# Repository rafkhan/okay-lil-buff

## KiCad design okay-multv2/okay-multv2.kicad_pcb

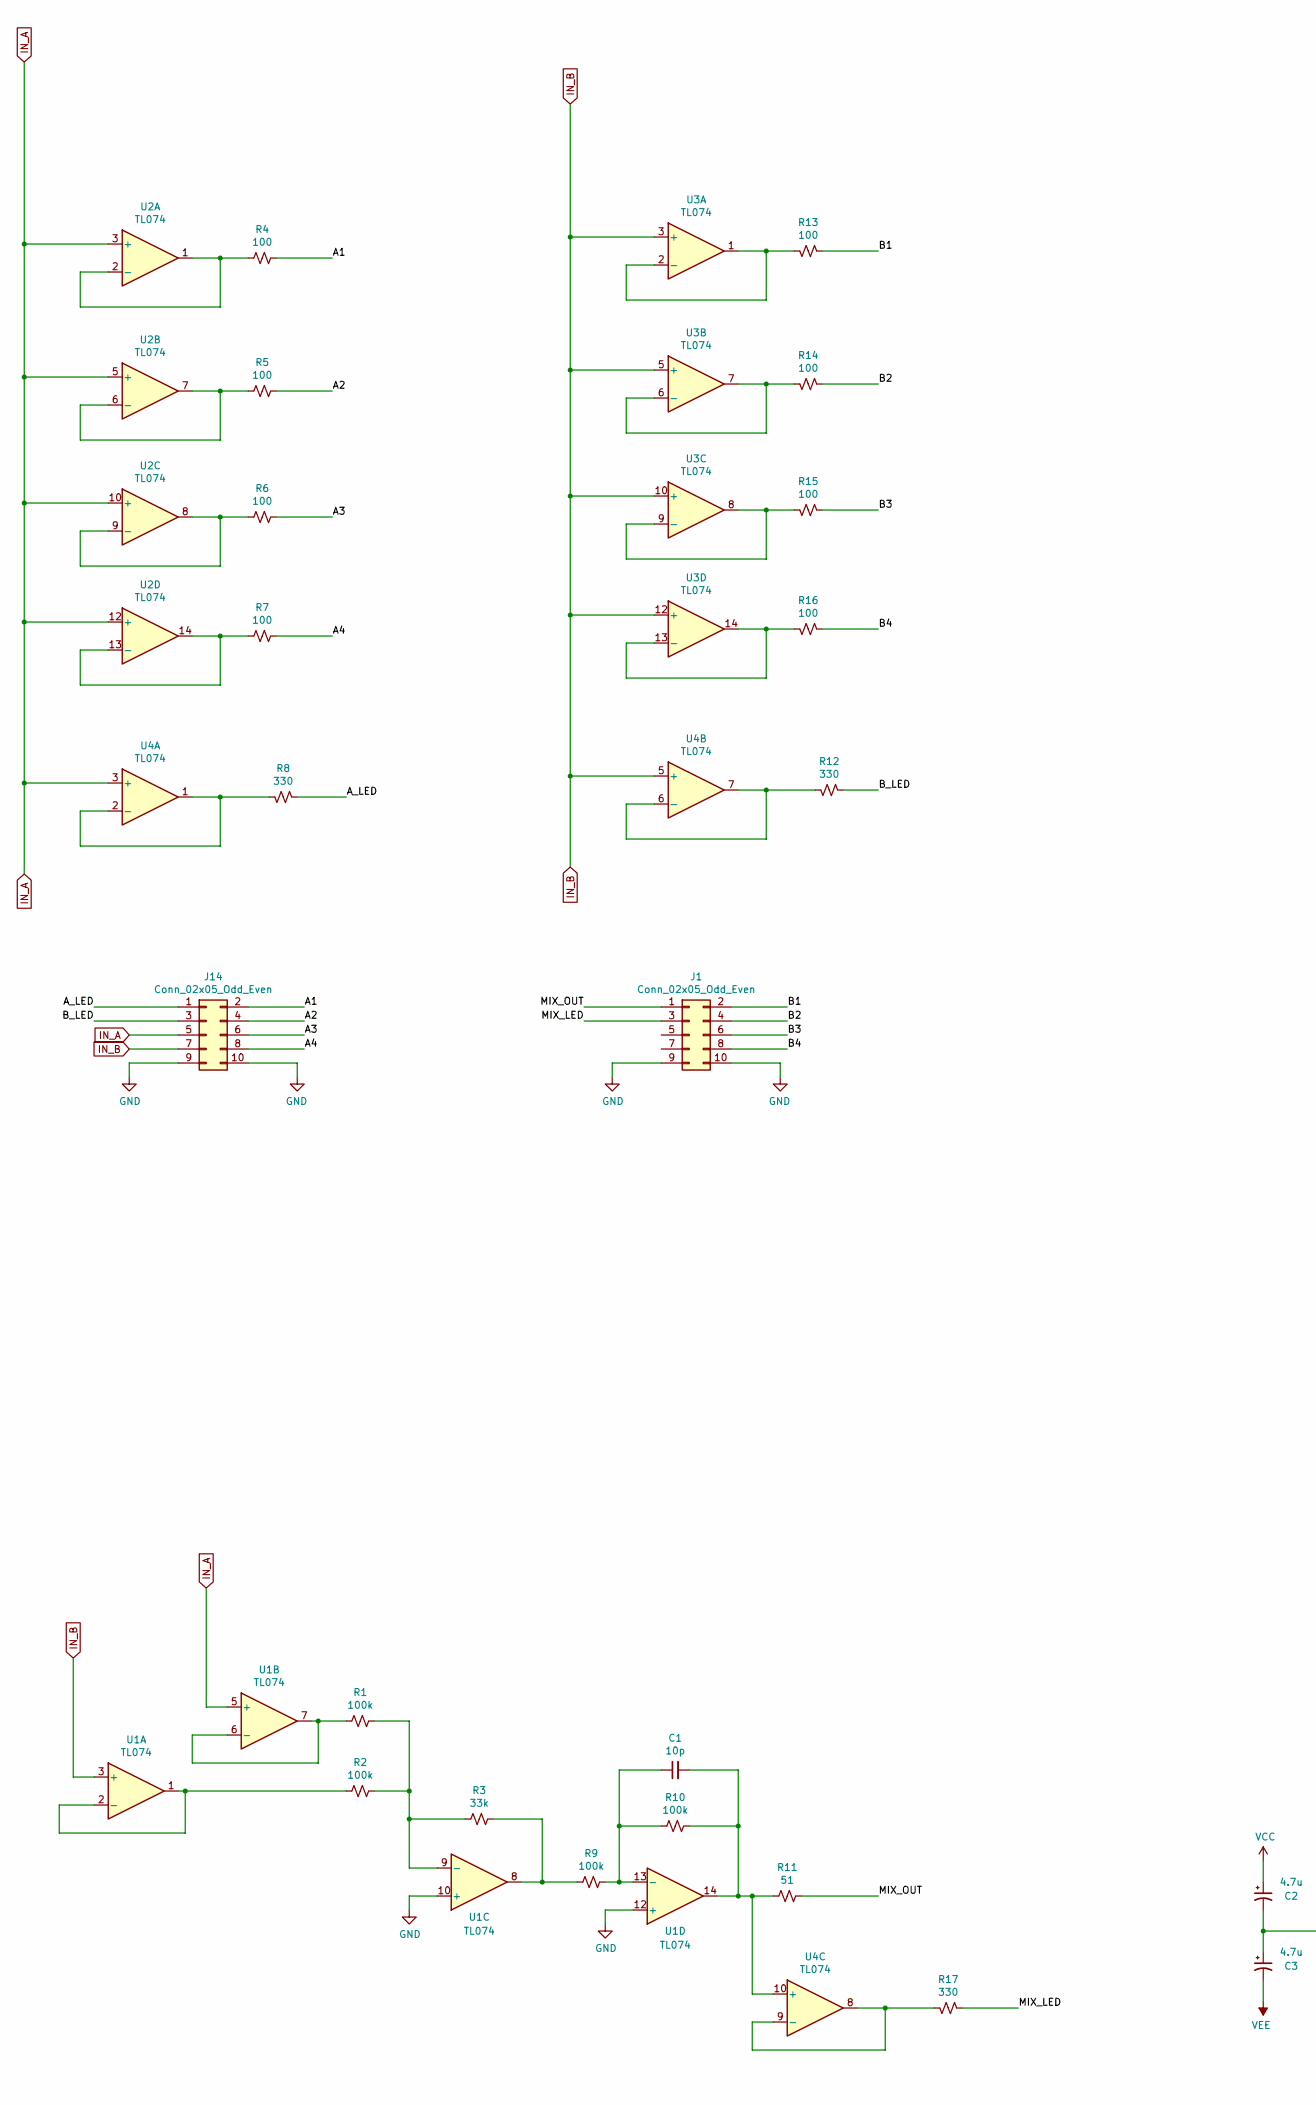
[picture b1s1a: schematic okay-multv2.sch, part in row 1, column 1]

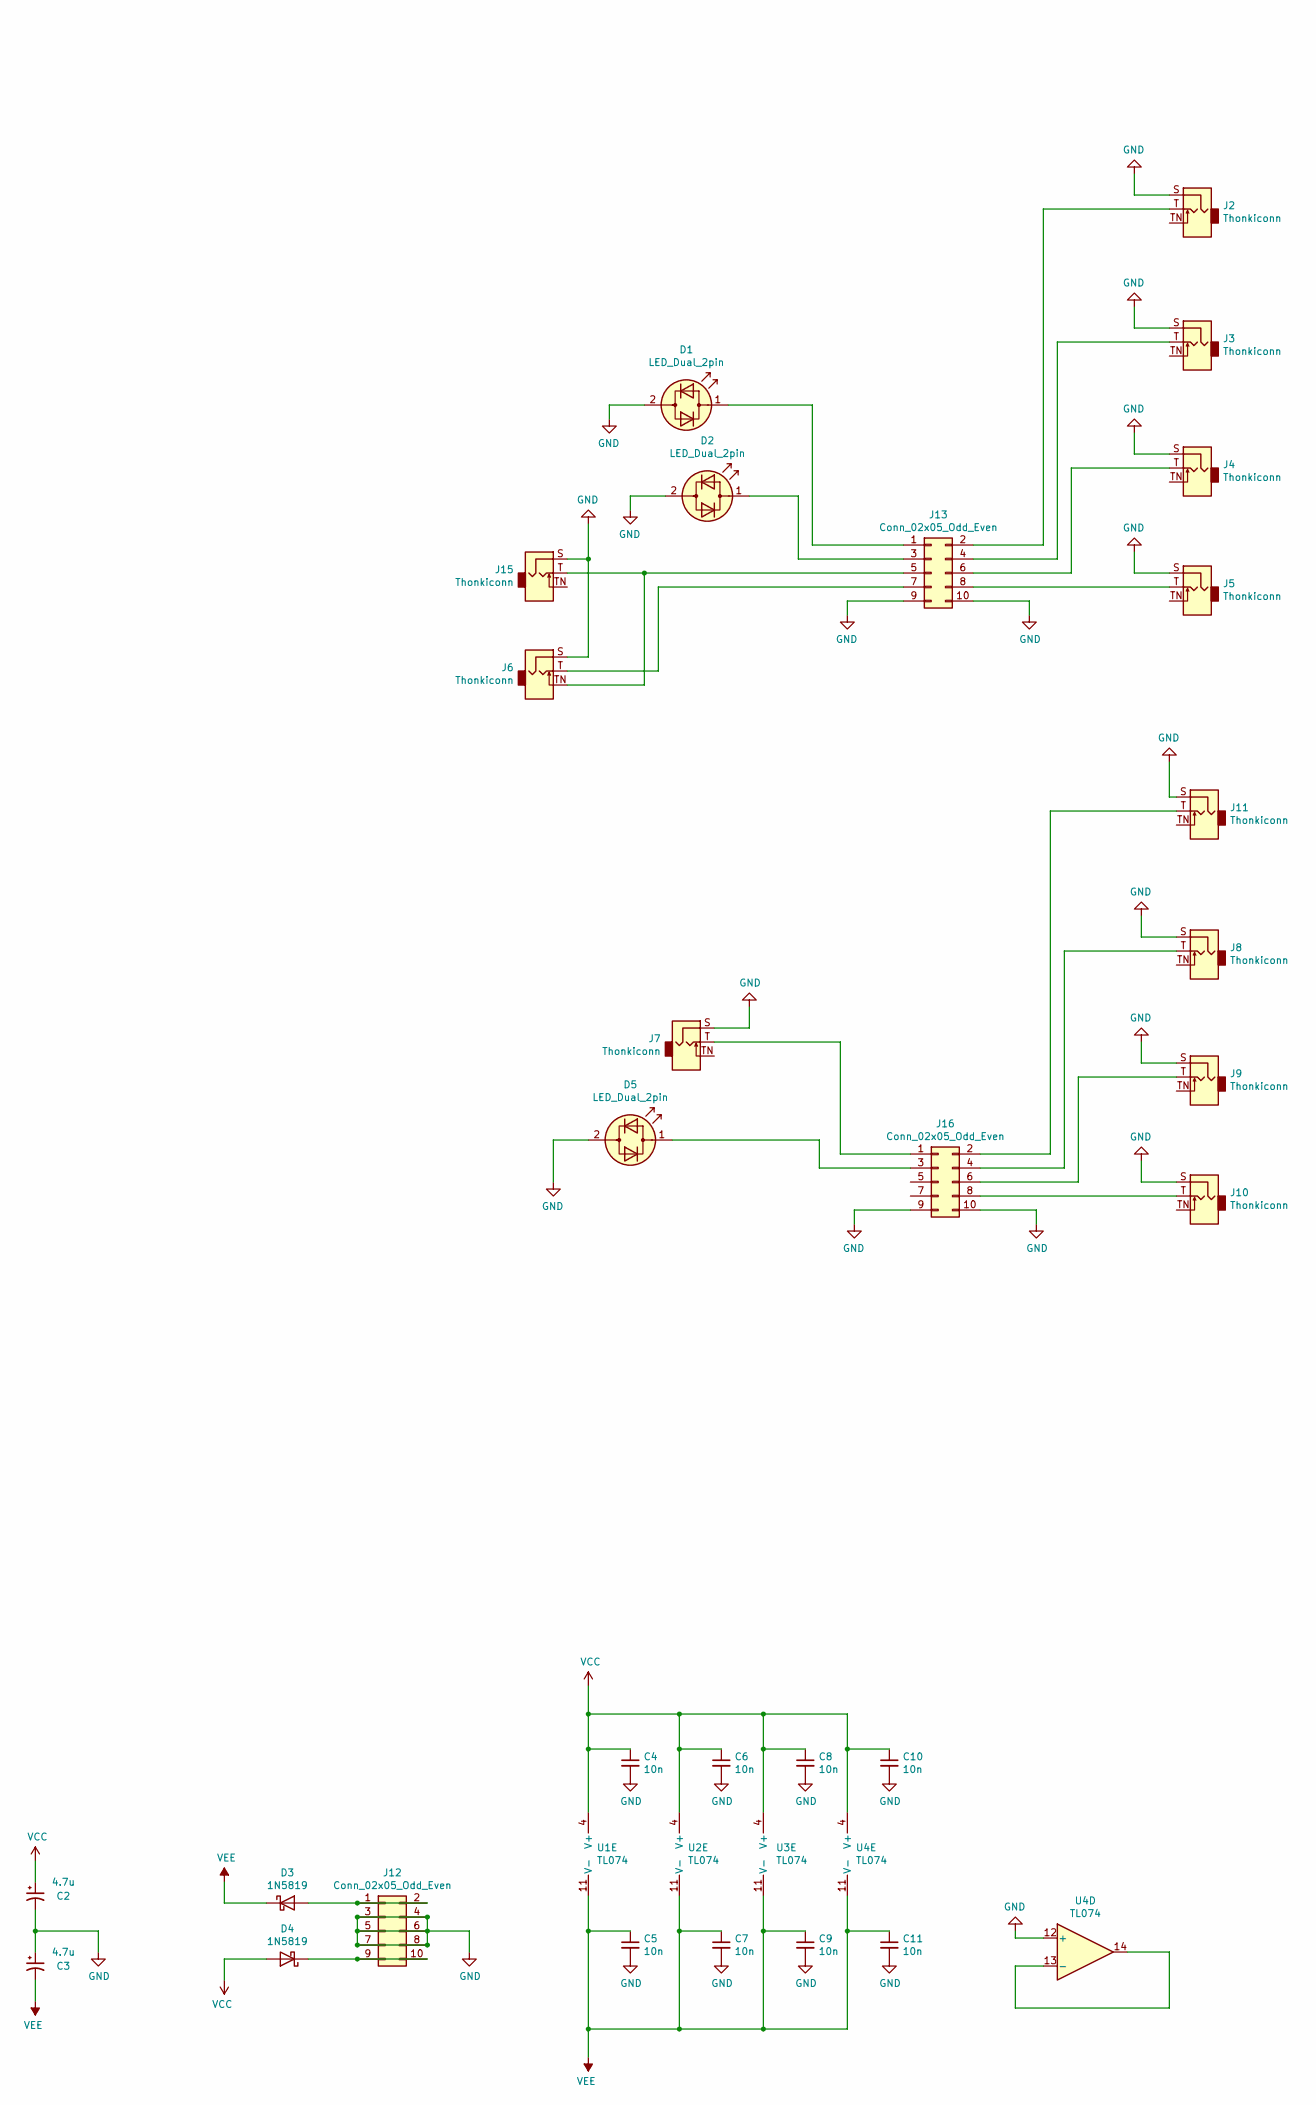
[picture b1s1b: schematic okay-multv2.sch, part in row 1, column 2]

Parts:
C1: 10p; C_0201_0603Metric
C2, C3: 4.7u; C_Elec_3x5.4
C4, C5, C6, C7, C8, C9, C10, C11: 10n; C_0201_0603Metric
D1, D2, D5: LED_Dual_2pin; LED_0805_2012Metric_Castellated
D3, D4: 1N5819; D_SOD-123F
J1, J12, J13, J14, J16: Conn_02x05_Odd_Even; PinHeader_2x05_P2.54mm_Vertical
J2, J3, J4, J5, J6, J7, J8, J9, J10, J11, J15: Thonkiconn; RAF__Jack_3.5mm_QingPu_WQP-PJ398SM_Vertical_CircularHoles
R1, R2, R9, R10: 100k; R_0201_0603Metric
R3: 33k; R_0201_0603Metric
R4, R5, R6, R7, R13, R14, R15, R16: 100; R_0201_0603Metric
R8, R12, R17: 330; R_0201_0603Metric
R11: 51; R_0201_0603Metric
U1, U2, U3, U4: TL074; SOIC-14_3.9x8.7mm_P1.27mm

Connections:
/A1: J14.2, R4.1
/A2: J14.4, R5.1
/A3: J14.6, R6.1
/A4: J14.8, R7.1
/A_LED: J14.1, R8.1
/B1: J1.2, R13.2
/B2: J1.4, R14.2
/B3: J1.6, R15.2
/B4: J1.8, R16.2
/B_LED: J14.3, R12.1
/MIX_LED: J1.3, R17.1
/MIX_OUT: J1.1, R11.2
GND: C2.2, C3.1, C4.2, C5.2, C6.2, C7.2, C8.2, C9.2, C10.2, C11.2, D1.2 (AK), D2.2 (AK), D5.2 (AK), J1.9, J1.10, J2.S, J3.S, J4.S, J5.S, J6.S, J7.S, J8.S, J9.S, J10.S, J11.S, J12.3, J12.4, J12.5, J12.6, J12.7, J12.8, J13.9, J13.10, J14.9, J14.10, J15.S, J16.9, J16.10, U1.10 (+), U1.12 (+), U4.12 (+)
IN_A: J14.5, U1.5 (+), U2.3 (+), U2.5 (+), U2.10 (+), U2.12 (+), U4.3 (+)
IN_B: J14.7, U1.3 (+), U3.3 (+), U3.5 (+), U3.10 (+), U3.12 (+), U4.5 (+)
unnamed: C1.1, R9.2, R10.1, U1.13 (-)
unnamed: C1.2, R10.2, R11.1, U1.14, U4.10 (+)
unnamed: D1.1 (KA), J13.1
unnamed: D2.1 (KA), J13.3
unnamed: D3.2 (A), J12.1, J12.2
unnamed: D4.1 (K), J12.9, J12.10
unnamed: D5.1 (KA), J16.3
unnamed: J10.T, J16.8
unnamed: J11.T, J16.2
unnamed: J2.T, J13.2
unnamed: J3.T, J13.4
unnamed: J6.TN, J13.5, J15.T
unnamed: J4.T, J13.6
unnamed: J6.T, J13.7
unnamed: J5.T, J13.8
unnamed: J7.T, J16.1
unnamed: J8.T, J16.4
unnamed: J9.T, J16.6
unnamed: R1.1, R2.2, R3.2, U1.9 (-)
unnamed: R1.2, U1.6 (-), U1.7
unnamed: R2.1, U1.1, U1.2 (-)
unnamed: R3.1, R9.1, U1.8
unnamed: R4.2, U2.1, U2.2 (-)
unnamed: R5.2, U2.6 (-), U2.7
unnamed: R6.2, U2.8, U2.9 (-)
unnamed: R7.2, U2.13 (-), U2.14
unnamed: R8.2, U4.1, U4.2 (-)
unnamed: R12.2, U4.6 (-), U4.7
unnamed: R13.1, U3.1, U3.2 (-)
unnamed: R14.1, U3.6 (-), U3.7
unnamed: R15.1, U3.8, U3.9 (-)
unnamed: R16.1, U3.13 (-), U3.14
unnamed: R17.2, U4.8, U4.9 (-)
unnamed: U4.13 (-), U4.14
VCC: C2.1, C4.1, C6.1, C8.1, C10.1, D4.2 (A), U1.4 (V+), U2.4 (V+), U3.4 (V+), U4.4 (V+)
VEE: C3.2, C5.1, C7.1, C9.1, C11.1, D3.1 (K), U1.11 (V-), U2.11 (V-), U3.11 (V-), U4.11 (V-)

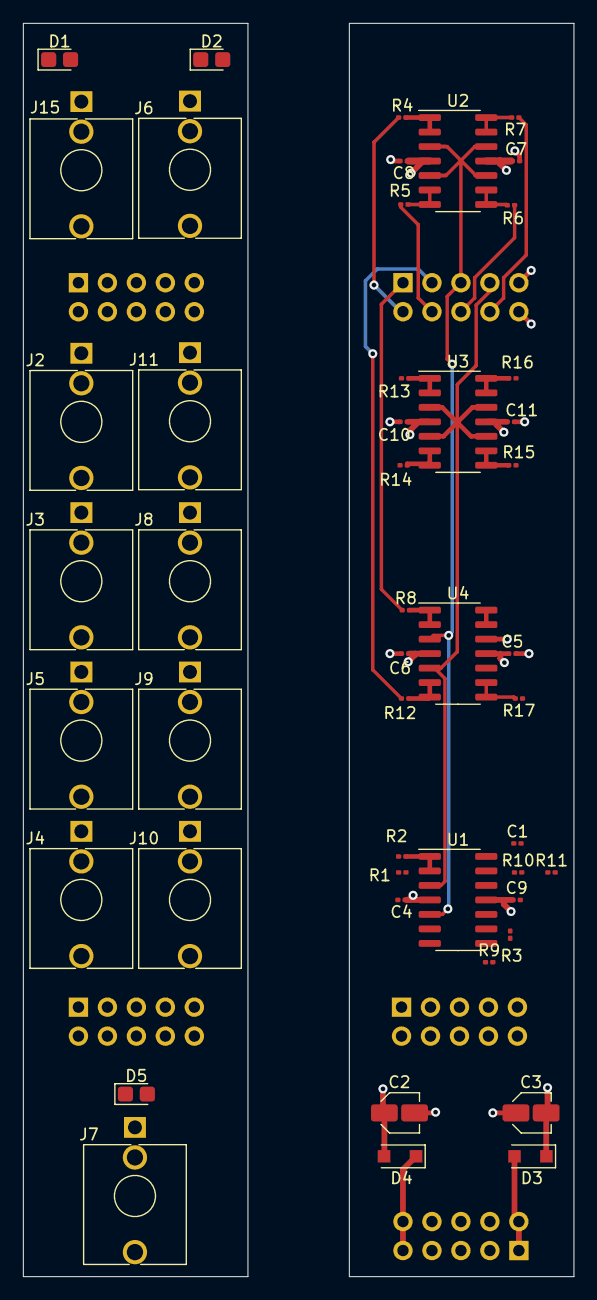
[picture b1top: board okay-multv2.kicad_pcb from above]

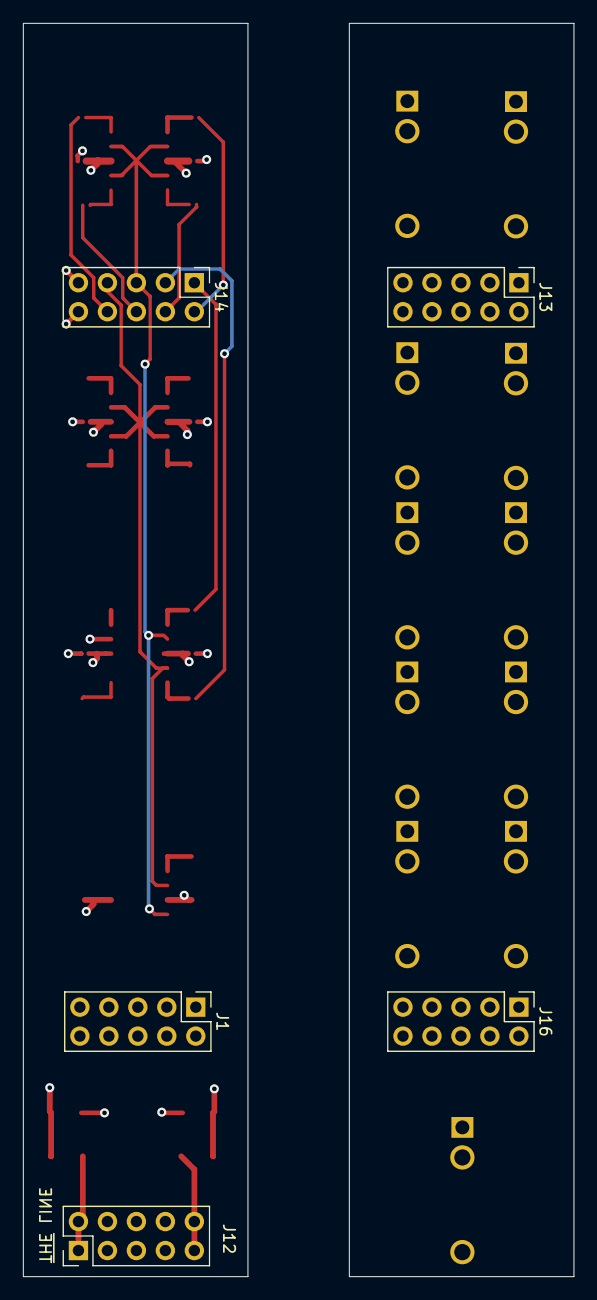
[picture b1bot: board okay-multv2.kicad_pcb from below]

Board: 4 copper layers, 48.3 x 109.9 mm, 53 parts (5 on the bottom side), 51 nets.

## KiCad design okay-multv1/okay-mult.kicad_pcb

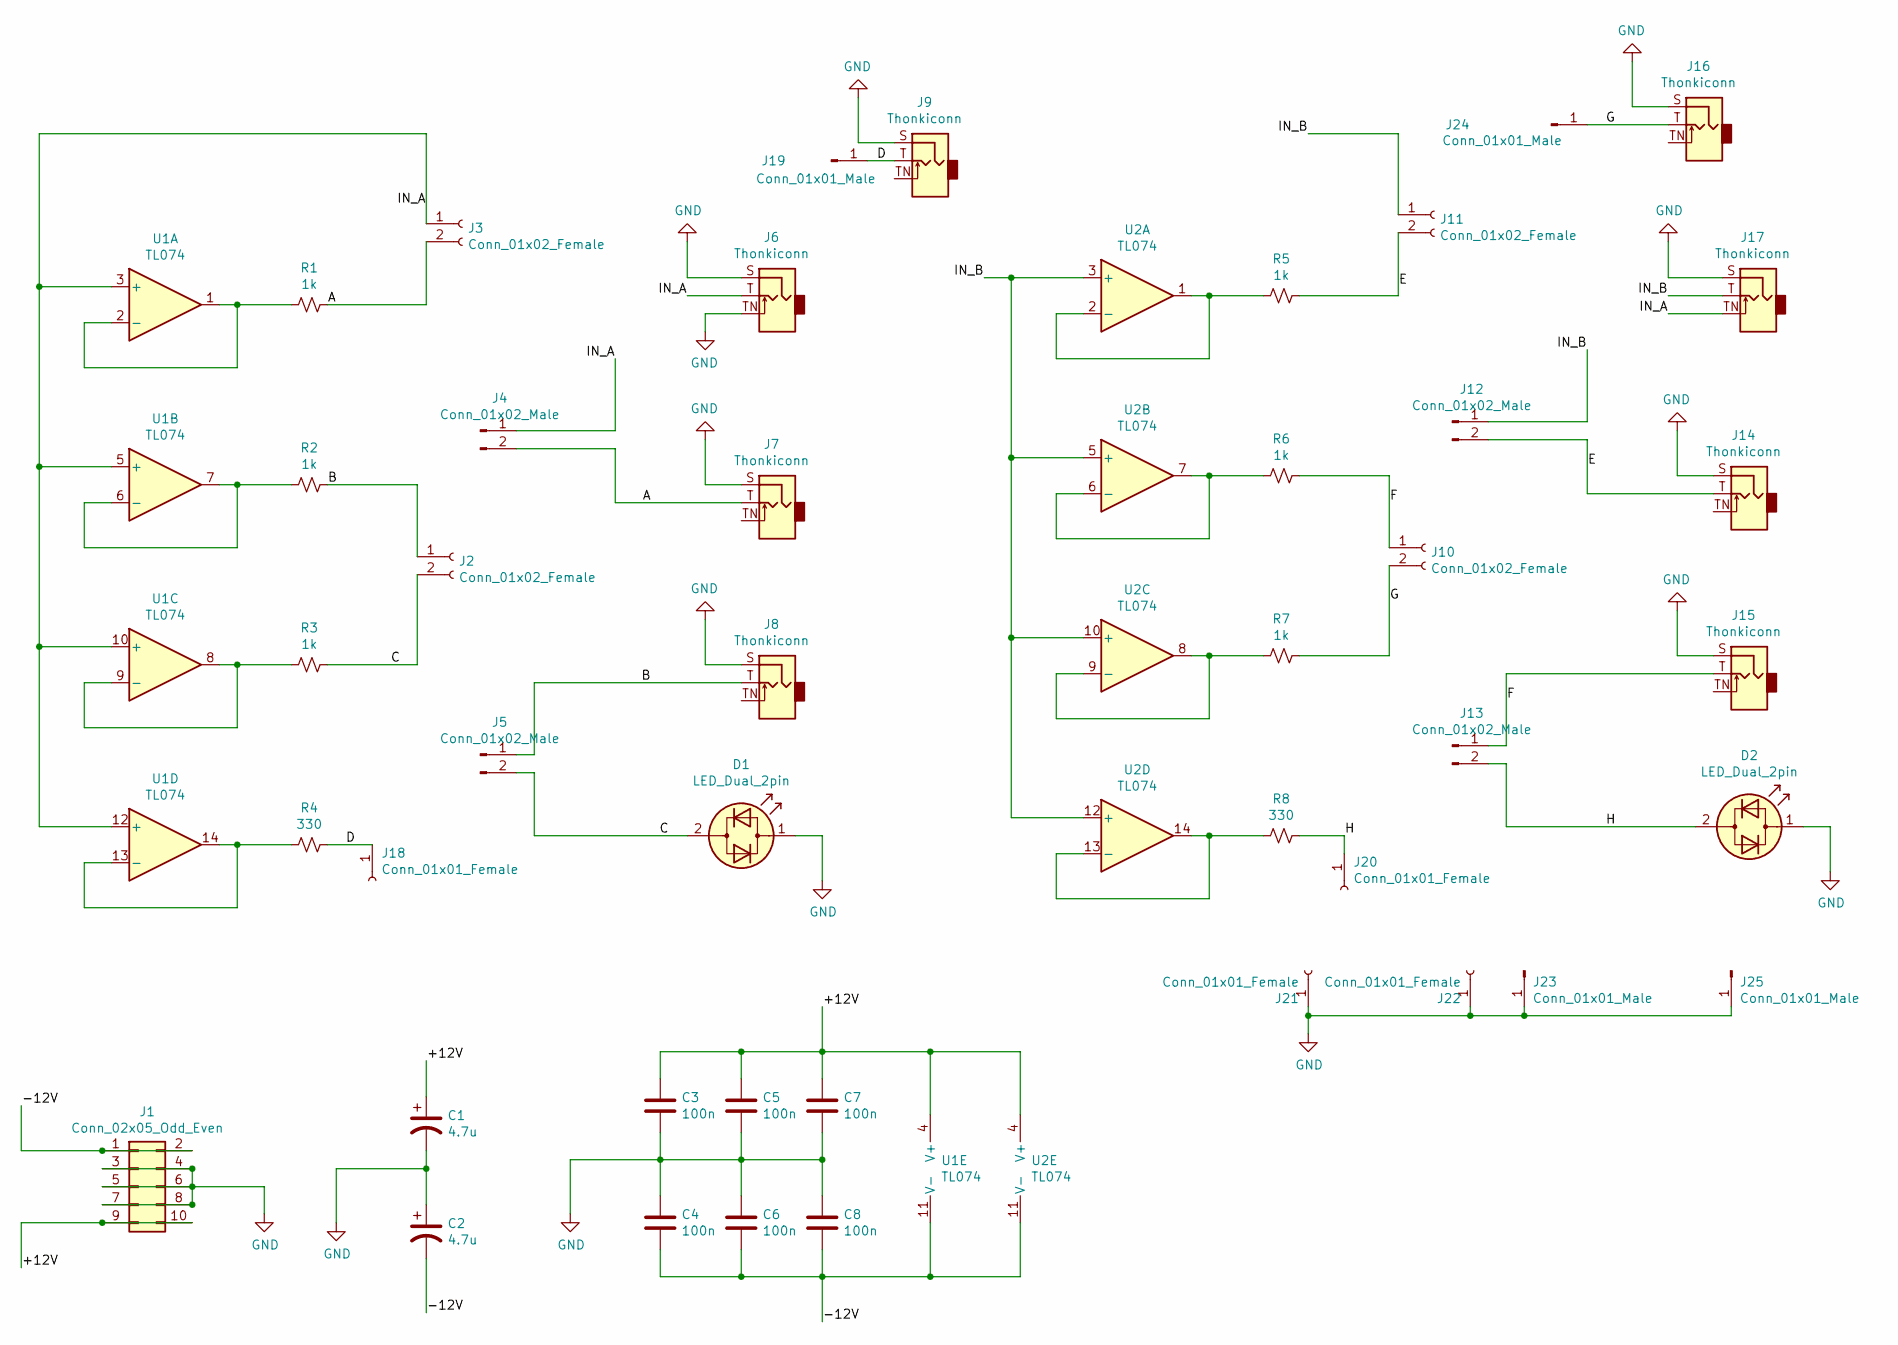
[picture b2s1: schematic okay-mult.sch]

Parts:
C1, C2: 4.7u; CP_Elec_3x5.4
C3, C4, C5, C6, C7, C8: 100n; C_0402_1005Metric
D1, D2: LED_Dual_2pin; LED_D3.0mm
J1: Conn_02x05_Odd_Even; PinHeader_2x05_P2.54mm_Vertical
J2, J3, J10, J11: Conn_01x02_Female; PinSocket_1x02_P2.54mm_Vertical
J4, J5, J12, J13: Conn_01x02_Male; PinHeader_1x02_P2.54mm_Vertical
J6, J8, J15, J17: Thonkiconn; RAF__NOGND__Jack_3.5mm_QingPu_WQP-PJ398SM_Vertical_Circular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
J7, J9, J14, J16: Thonkiconn; RAF__Jack_3.5mm_QingPu_WQP-PJ398SM_Vertical_CircularHoles
J18, J20, J21, J22: Conn_01x01_Female; PinSocket_1x01_P2.54mm_Vertical
J19, J23, J24, J25: Conn_01x01_Male; PinHeader_1x01_P2.54mm_Vertical
R1, R2, R3, R5, R6, R7: 1k; R_0402_1005Metric
R4, R8: 330; R_0402_1005Metric
U1: TL074; SOIC-14_3.9x8.7mm_P1.27mm
U2: TL074

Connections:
/+12V: C1.1, C3.1, C5.1, C7.1, J1.9, J1.10, U1.4 (V+), U2.4 (V+)
/-12V: C2.2, C4.2, C6.2, C8.2, J1.1, J1.2, U1.11 (V-), U2.11 (V-)
/A: J3.2, J4.2, J7.T, R1.1
/B: J2.1, J5.1, J8.T, R2.1
/C: D1.2 (AK), J2.2, J5.2, R3.1
/D: J9.T, J18.1, J19.1, R4.1
/E: J11.2, J12.2, J14.T, R5.1
/F: J10.1, J13.1, J15.T, R6.1
/G: J10.2, J16.T, J24.1, R7.1
/H: D2.2 (AK), J13.2, J20.1, R8.1
/IN_A: J3.1, J4.1, J6.T, J17.TN, U1.3 (+), U1.5 (+), U1.10 (+), U1.12 (+)
/IN_B: J11.1, J12.1, J17.T, U2.3 (+), U2.5 (+), U2.10 (+), U2.12 (+)
GND: C1.2, C2.1, C3.2, C4.1, C5.2, C6.1, C7.2, C8.1, D1.1 (KA), D2.1 (KA), J1.3, J1.4, J1.5, J1.6, J1.7, J1.8, J6.S, J6.TN, J7.S, J8.S, J9.S, J14.S, J15.S, J16.S, J17.S, J21.1, J22.1, J23.1, J25.1
unnamed: R1.2, U1.1, U1.2 (-)
unnamed: R2.2, U1.6 (-), U1.7
unnamed: R3.2, U1.8, U1.9 (-)
unnamed: R4.2, U1.13 (-), U1.14
unnamed: R5.2, U2.1, U2.2 (-)
unnamed: R6.2, U2.6 (-), U2.7
unnamed: R7.2, U2.8, U2.9 (-)
unnamed: R8.2, U2.13 (-), U2.14

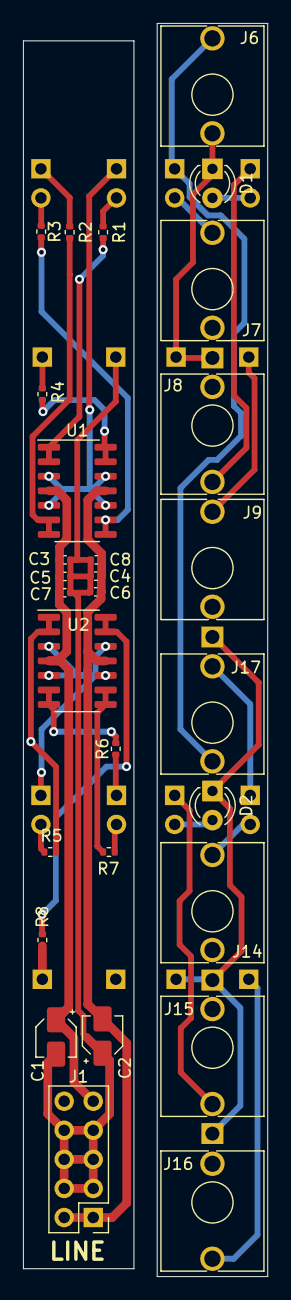
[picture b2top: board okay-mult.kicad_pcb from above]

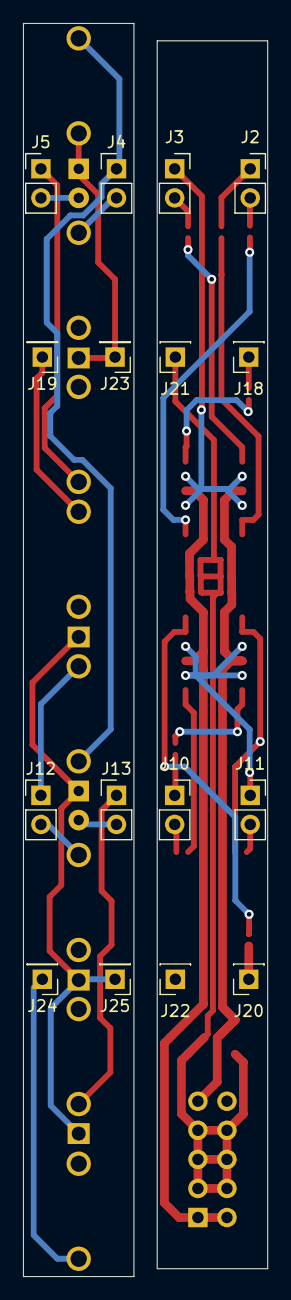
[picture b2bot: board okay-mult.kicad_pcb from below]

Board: 2 copper layers, 21.3 x 109.5 mm, 45 parts (16 on the bottom side), 21 nets.

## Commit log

2021-02-16 Bigger fatter traces
2021-03-10 Update v2
